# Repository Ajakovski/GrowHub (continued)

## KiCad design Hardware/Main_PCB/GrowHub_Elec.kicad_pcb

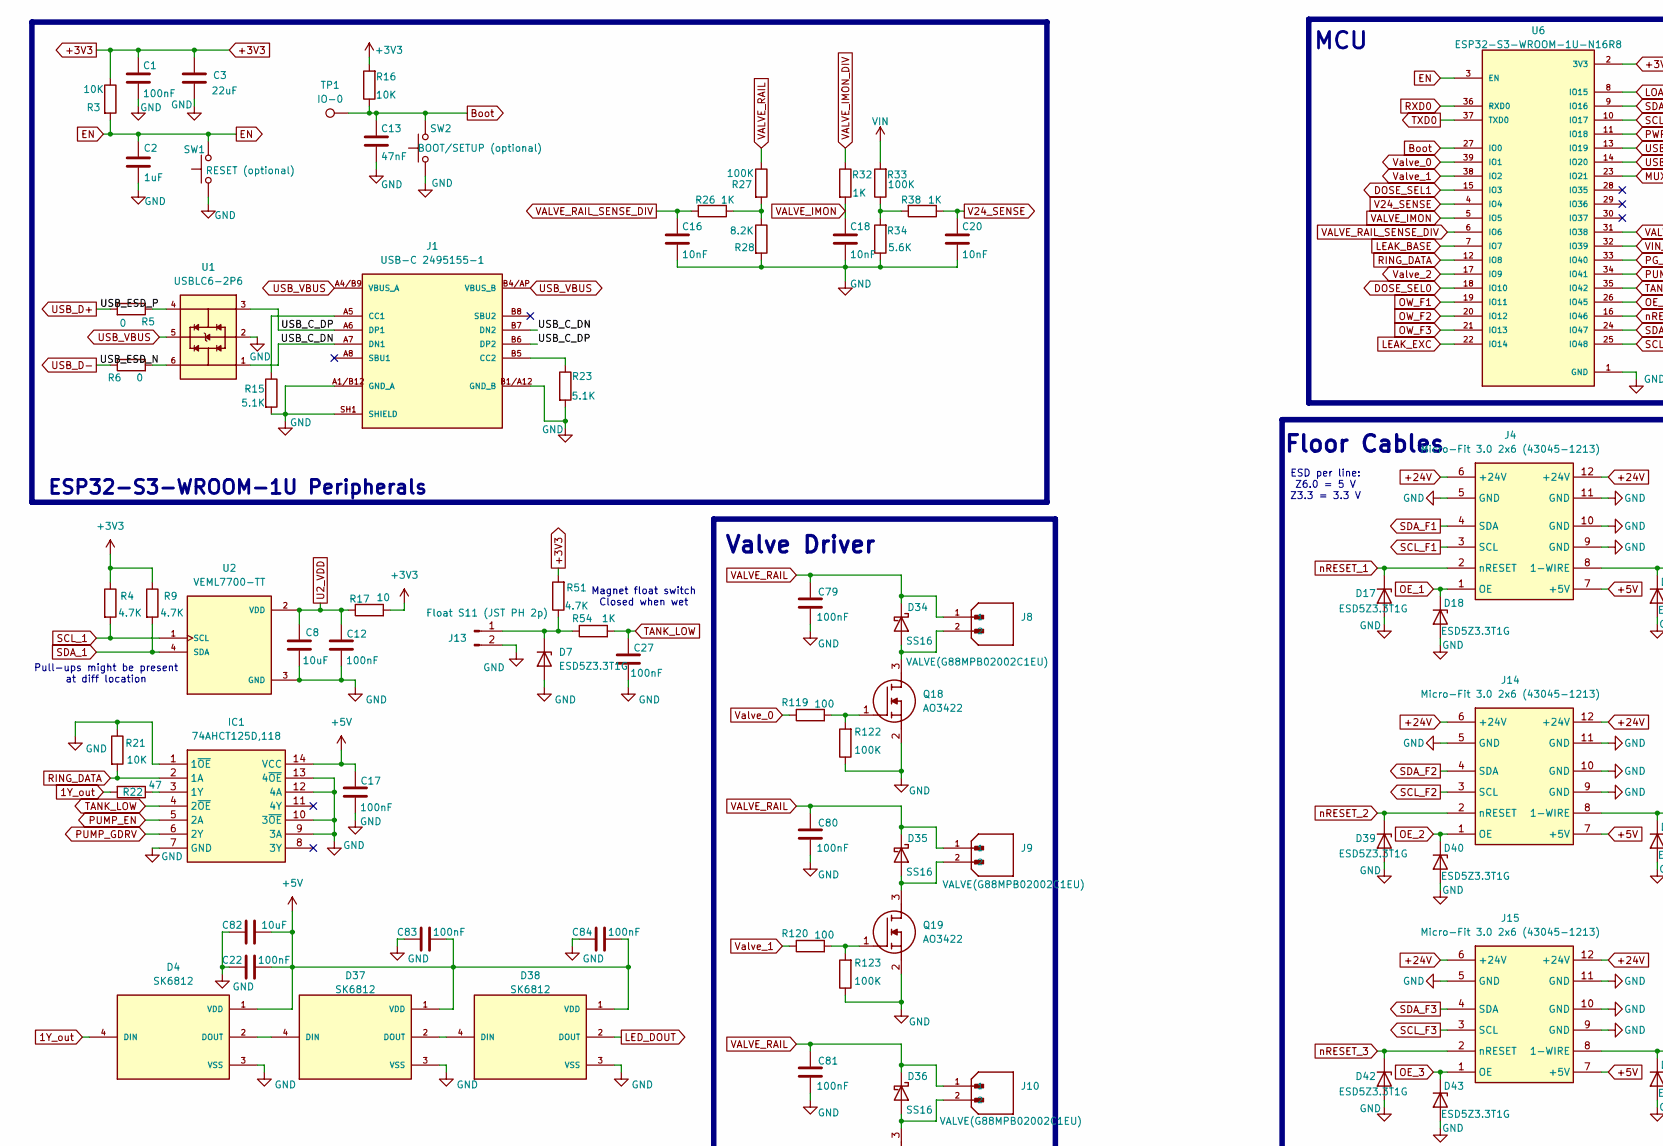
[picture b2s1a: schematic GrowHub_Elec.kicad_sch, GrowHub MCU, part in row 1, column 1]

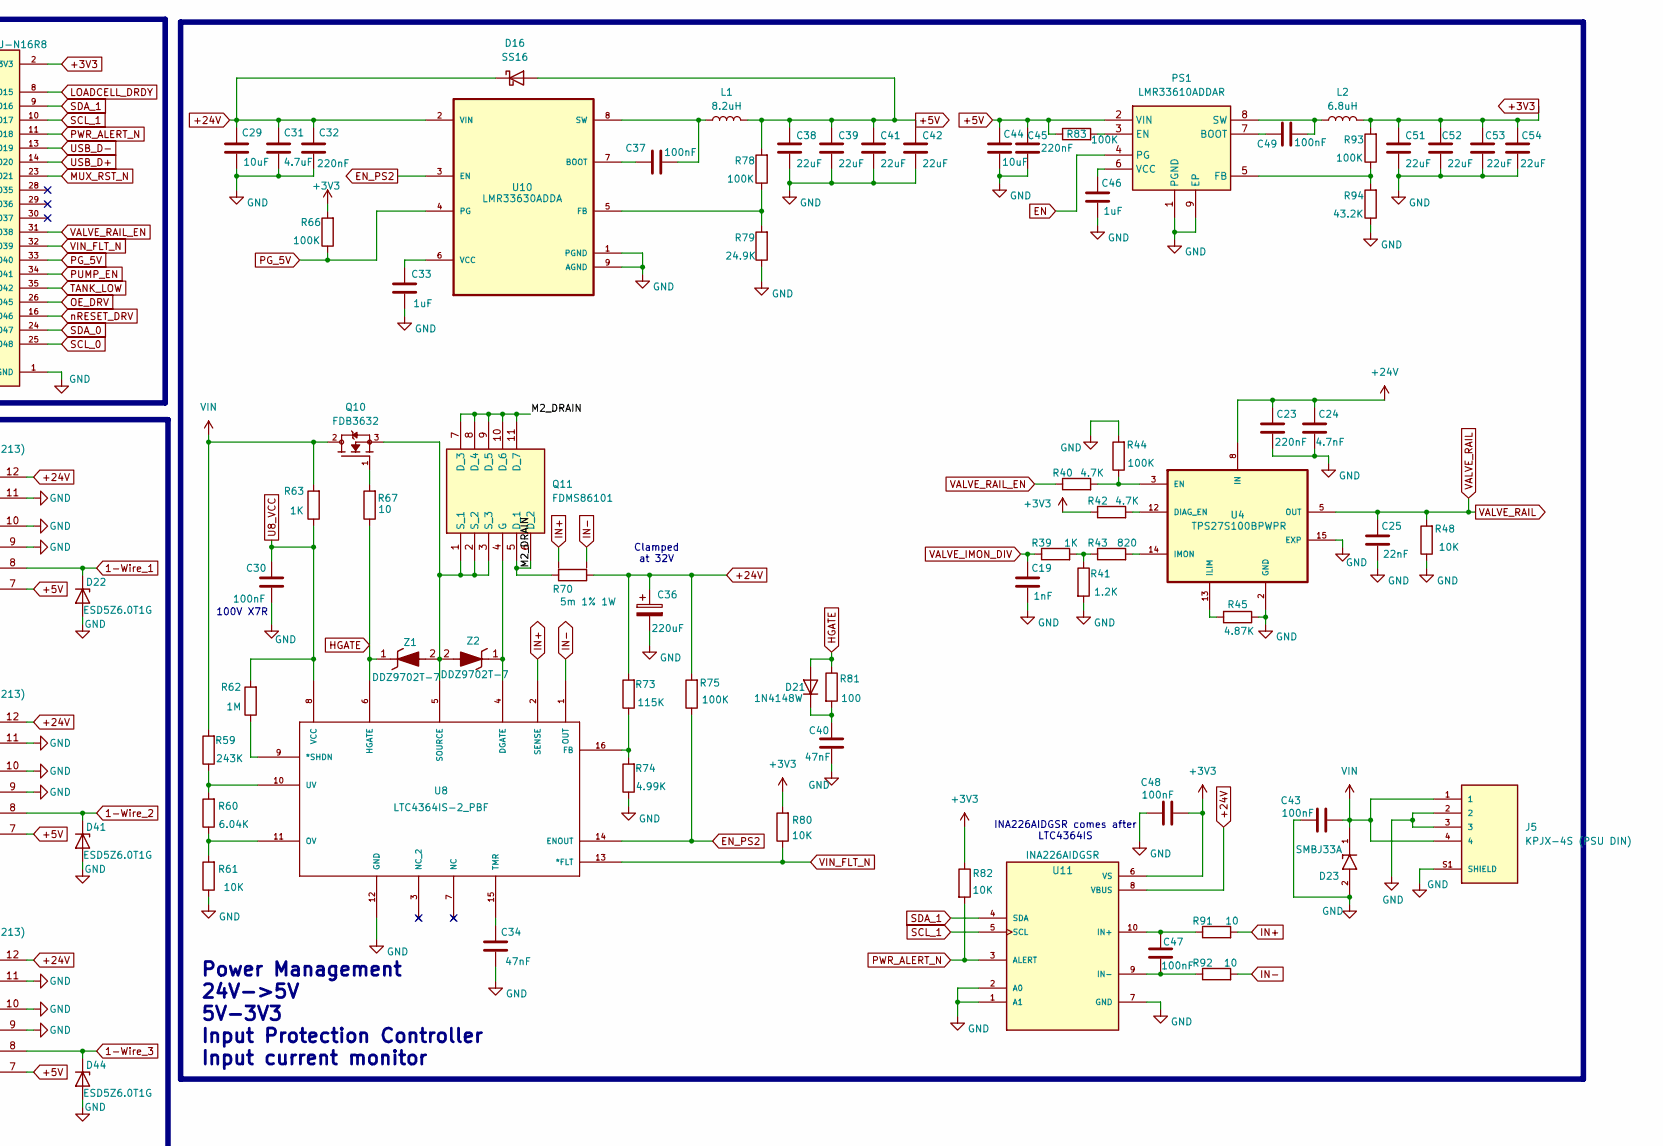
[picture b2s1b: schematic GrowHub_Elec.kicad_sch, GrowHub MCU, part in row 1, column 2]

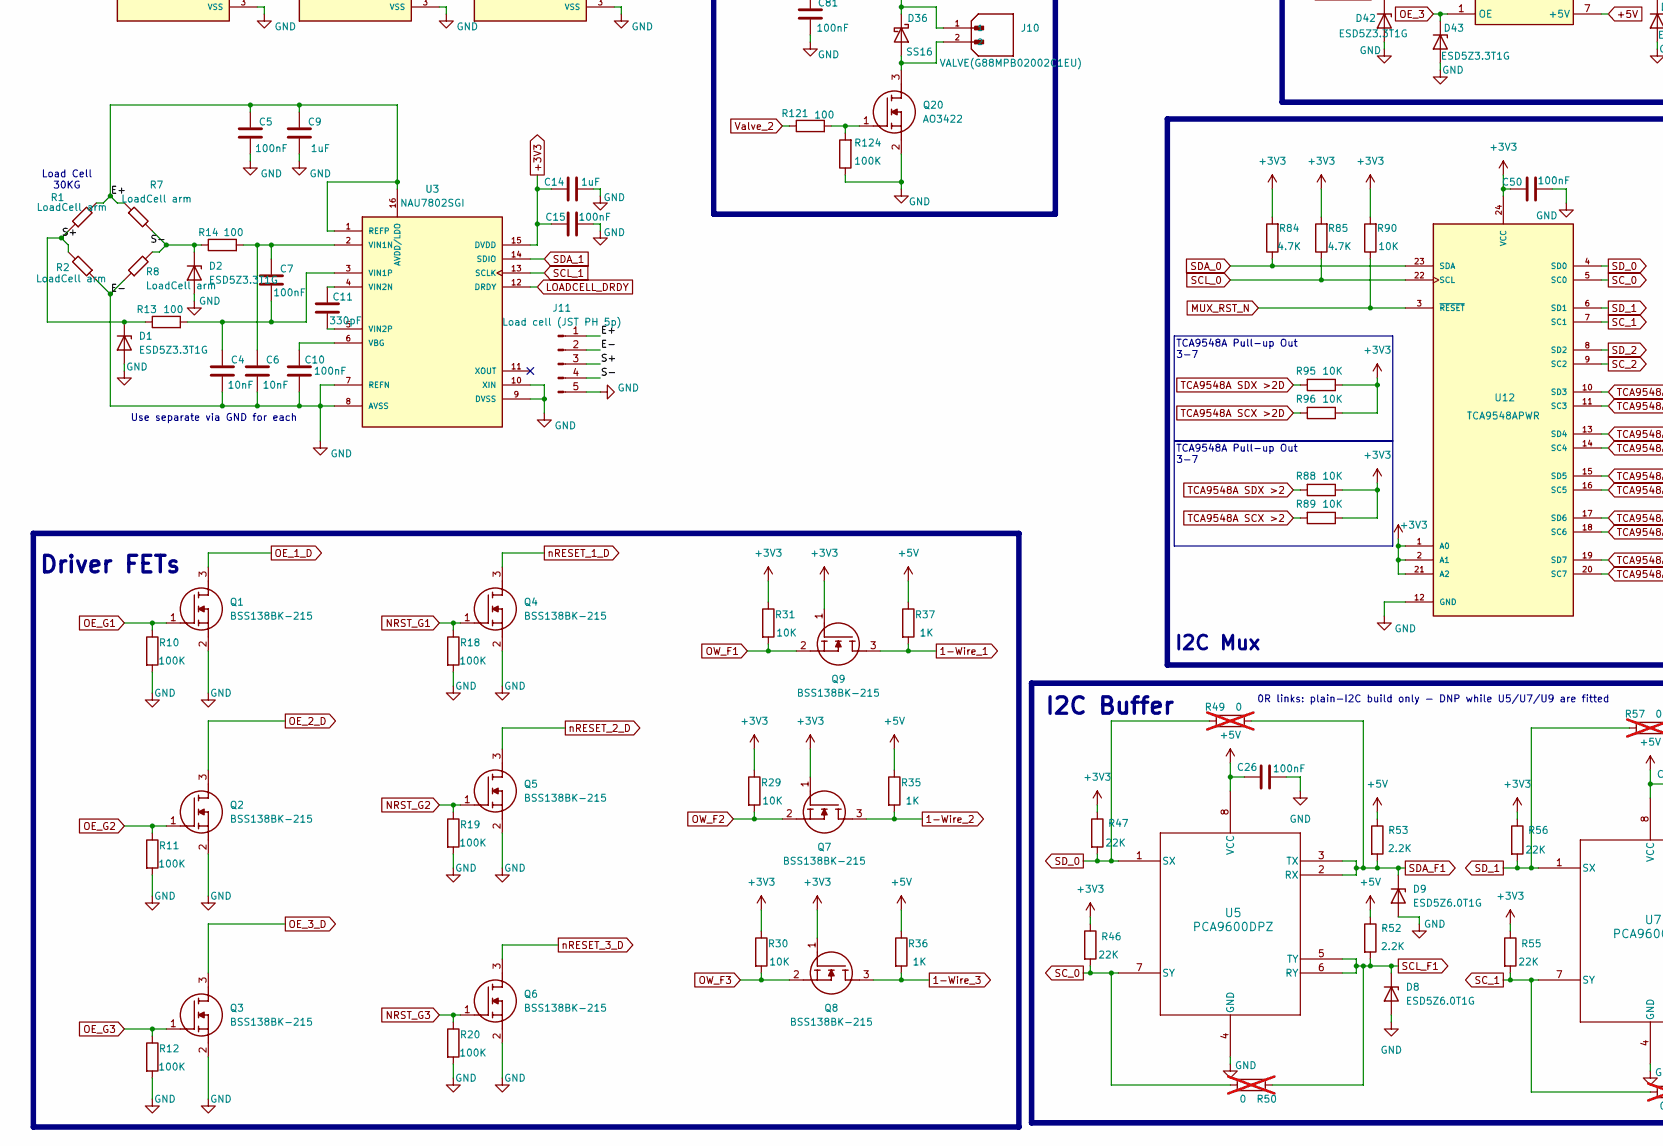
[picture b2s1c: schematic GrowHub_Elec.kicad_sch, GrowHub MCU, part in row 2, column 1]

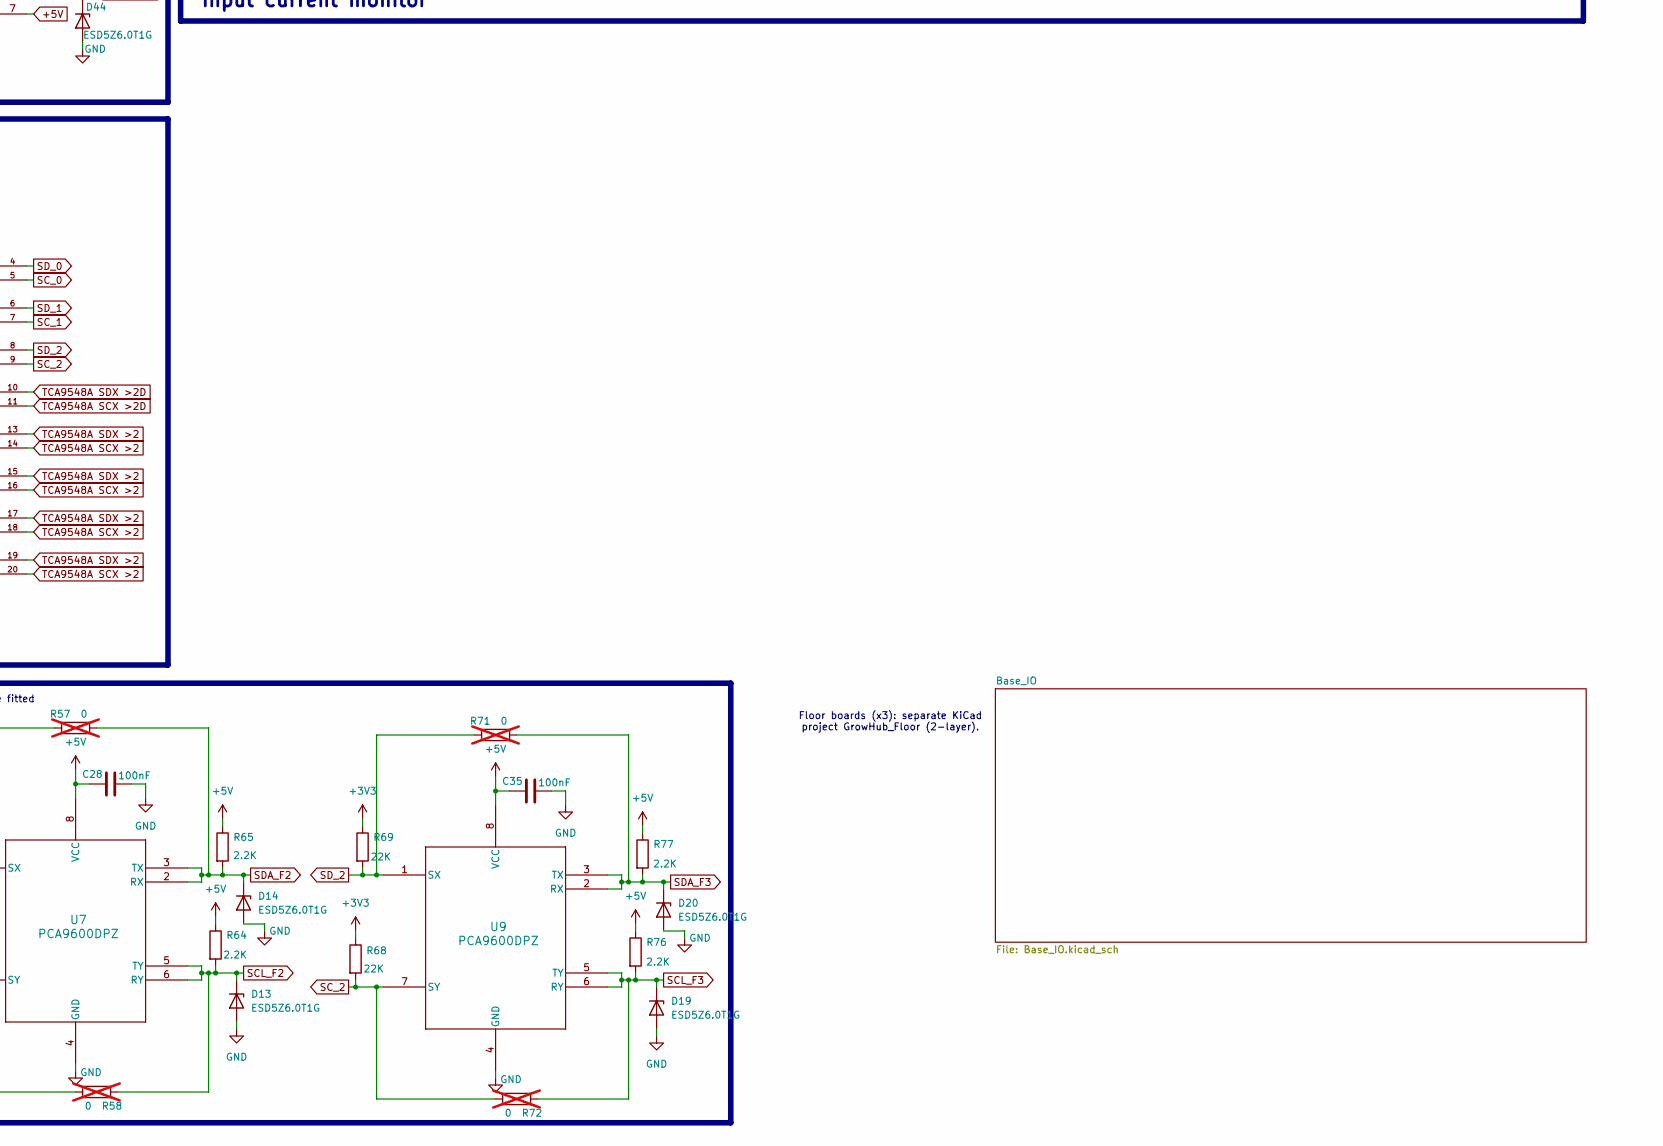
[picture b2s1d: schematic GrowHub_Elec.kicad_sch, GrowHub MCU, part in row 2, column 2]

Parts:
C1, C5, C7, C10, C12, C15, C17, C22, C26, C27, C28, C35, C37, C48, C49, C50, C83, C84: 100nF; C_0603_1608Metric; Rating 16V X7R
C2, C9, C14, C33, C46: 1uF; C_0603_1608Metric; Rating 16V X7R
C3, C51, C52, C53, C54: 22uF; C_1206_3216Metric; Rating 10V X7R
C4, C6: 10nF; C_0603_1608Metric; Rating 50V C0G
C8: 10uF; C_0805_2012Metric; Rating 10V X7R
C11: 330pF; C_0603_1608Metric; Rating 50V C0G
C13: 47nF; C_0603_1608Metric; Rating 16V X7R
C16, C18, C20: 10nF; C_0603_1608Metric; Rating 16V X7R
C19: 1nF; C_0603_1608Metric; Rating 50V C0G
C23, C32: 220nF; C_0603_1608Metric; Rating 50V X7R
C24: 4.7nF; C_0603_1608Metric; Rating 50V X7R
C25: 22nF; C_0603_1608Metric; Rating 50V X7R
C29: 10uF; C_1210_3225Metric; Rating 50V X7R
C30, C43: 100nF; C_0805_2012Metric; Rating 100V X7R
C31: 4.7uF; C_1210_3225Metric; Rating 50V X7R
C34: 47nF; C_0603_1608Metric; Rating 25V X7R
C36: 220uF; CP_Elec_10x10.5; Rating 50V low-ESR aluminium, >=105 C
C38, C39, C41, C42: 22uF; C_1206_3216Metric; Rating 16V X7R
C40: 47nF; C_0603_1608Metric; Rating 50V X7R
C44: 10uF; C_0805_2012Metric; Rating 16V X7R
C45: 220nF; C_0603_1608Metric; Rating 16V X7R
C47, C79, C80, C81: 100nF; C_0603_1608Metric; Rating 50V X7R
C82: 10uF; C_1206_3216Metric; Rating 16V X7R
D1, D2, D7, D17, D18, D39, D40, D42, D43: ESD5Z3.3T1G; D_SOD-523
D4, D37, D38: SK6812; LED_SK6812; PARTREV 03
D8, D9, D13, D14, D19, D20, D22, D41, D44: ESD5Z6.0T1G; D_SOD-523
D16, D34, D35, D36: SS16; D_SMA
D21: 1N4148W; D_SOD-123
D23: SMBJ33A; D_SMB; PARTREV 20 - 2
IC1: 74AHCT125D,118; SOIC-14_3.9x8.7mm_P1.27mm; Mouser Part Number 771-AHCT125D118
J1: USB-C 2495155-1; TE_2495155-1; PARTREV A
J4, J14, J15: Micro-Fit 3.0 2x6 (43045-1213); 0430451213; Mouser Part Number N/A
J5: KPJX-4S (PSU DIN); KYCON_KPJX-4S; PARTREV A12
J8, J9, J10: VALVE(G88MPB02002C1EU); AMPHENOL_G88MPB02002C1EU; PARTREV C
J11: Load cell (JST PH 5p); JST_PH_B5B-PH-K_1x05_P2.00mm_Vertical
J13: Float S11 (JST PH 2p); JST_PH_B2B-PH-K_1x02_P2.00mm_Vertical
L1: 8.2uH; L_Coilcraft_XAL1010-XXX; MPN Coilcraft XAL1010-822MED (12.9 mOhm max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
L2: 6.8uH; L_Coilcraft_XAL7070-XXX; MPN Coilcraft XAL7070-682MEC (19.6 mOhm max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
PS1: LMR33610ADDAR; Texas_HSOP-8-1EP_3.9x4.9mm_P1.27mm_ThermalVias; Mouser Part Number 595-LMR33610ADDAR
Q1, Q2, Q3, Q4, Q5, Q6, Q7, Q8, Q9: BSS138BK-215; SOT-23
Q10: FDB3632; TO254P1524X483-3N; PARTREV 4
Q11: FDMS86101; FDMS86252; Mouser Part Number 512-FDMS86101
Q18, Q19, Q20: AO3422; SOT-23
R1, R2, R7, R8: LoadCell arm
R3, R16, R21, R29, R30, R31, R48, R80, R82, R88, R89, R90, R95, R96: 10K; R_0603_1608Metric
R4, R9, R40, R42, R51, R84, R85: 4.7K; R_0603_1608Metric
R5, R6: 0; R_0603_1608Metric
R10, R11, R12, R18, R19, R20, R44, R66, R75, R83, R122, R123, R124: 100K; R_0603_1608Metric
R13, R14, R81, R119, R120, R121: 100; R_0603_1608Metric
R15, R23: 5.1K; R_0603_1608Metric
R17, R67, R91, R92: 10; R_0603_1608Metric
R22: 47; R_0603_1608Metric
R26, R32, R38: 1K; R_0603_1608Metric; Tolerance 1%
R27, R33, R78, R93: 100K; R_0603_1608Metric; Tolerance 1%
R28: 8.2K; R_0603_1608Metric; Tolerance 1%
R34: 5.6K; R_0603_1608Metric; Tolerance 1%
R35, R36, R37, R39, R54, R63: 1K; R_0603_1608Metric
R41: 1.2K; R_0603_1608Metric; Tolerance 1%
R43: 820; R_0603_1608Metric; Tolerance 1%
R45: 4.87K; R_0603_1608Metric; Tolerance 1%
R46, R47, R55, R56, R68, R69: 22K; R_0603_1608Metric
R49, R50, R57, R58, R71, R72: 0; R_0603_1608Metric; not fitted
R52, R53, R64, R65, R76, R77: 2.2K; R_0603_1608Metric
R59: 243K; R_0603_1608Metric; Tolerance 1%
R60: 6.04K; R_0603_1608Metric; Tolerance 1%
R61: 10K; R_0603_1608Metric; Tolerance 1%
R62: 1M; R_0603_1608Metric
R70: 5m 1% 1W; R_Shunt_Vishay_WSK2512_6332Metric_T1.19mm; MPN Vishay WSK2512R0050FEA (5 mOhm 1% 1 W, 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
R73: 115K; R_0603_1608Metric; Tolerance 1%
R74: 4.99K; R_0603_1608Metric; Tolerance 1%
R79: 24.9K; R_0603_1608Metric; Tolerance 1%
R94: 43.2K; R_0603_1608Metric; Tolerance 1%
SW1: RESET (optional); SW_SPST_TL3342
SW2: BOOT/SETUP (optional); SW_SPST_TL3342
TP1: IO-0; TestPoint_Pad_D1.5mm
U1: USBLC6-2P6; SOT-666; PARTREV 5
U2: VEML7700-TT; XDCR_VEML7700-TT; PARTREV 1.6
U3: NAU7802SGI; SOIC-16_3.9x9.9mm_P1.27mm; PARTREV 2.6
U4: TPS27S100BPWPR; IC_TPS27S100BPWPR
U5, U7, U9: PCA9600DPZ; TSSOP-8_3x3mm_P0.65mm
U6: ESP32-S3-WROOM-1U-N16R8; XCVR_ESP32-S3-WROOM-1U-N16R8; PARTREV v1.1
U8: LTC4364IS-2_PBF; SOIC-16_3.9x9.9mm_P1.27mm; MANUFACTURER_PART_NUMBER ltc4364is2#pbf
U10: LMR33630ADDA; Texas_HSOP-8-1EP_3.9x4.9mm_P1.27mm_ThermalVias
U11: INA226AIDGSR; TSSOP-10_3x3mm_P0.5mm; PARTREV B
U12: TCA9548APWR; TSSOP-24_4.4x7.8mm_P0.65mm; PARTREV G
Z1, Z2: DDZ9702T-7; D_SOD-523; Mouser Part Number 621-DDZ9702T-7

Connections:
1-Wire_1: D22.1 (K), J4.8 (1-WIRE), Q9.3 (D), R37.2
1-Wire_2: D41.1 (K), J14.8 (1-WIRE), Q7.3 (D), R35.2
1-Wire_3: D44.1 (K), J15.8 (1-WIRE), Q8.3 (D), R36.2
1Y_out: D4.4 (DIN), R22.2
+3V3: C1.1, C3.1, C14.1, C15.1, C48.1, C50.2, C51.2, C52.2, C53.2, C54.2, L2.2, Q7.1 (G), Q8.1 (G), Q9.1 (G), R3.1, R4.1, R9.1, R16.2, R17.2, R29.1, R30.1, R31.1, R42.1, R46.1, R47.1, R51.2, R55.1, R56.1, R66.2, R68.1, R69.1, R80.2, R82.1, R84.2, R85.2, R88.1, R89.1, R90.2, R93.2, R95.1, R96.1, U3.15 (DVDD), U6.2 (3V3), U11.6 (VS), U12.1 (A0), U12.2 (A1), U12.21 (A2), U12.24 (VCC); also elsewhere on the board
+5V: C17.1, C22.2, C26.2, C28.2, C35.2, C38.2, C39.2, C41.2, C42.2, C44.2, C45.2, C82.2, C83.2, C84.2, D4.1 (VDD), D16.2 (A), D37.1 (VDD), D38.1 (VDD), IC1.14 (VCC), J4.7 (+5V), J14.7 (+5V), J15.7 (+5V), L1.2, PS1.2 (VIN), R35.1, R36.1, R37.1, R52.1, R53.1, R64.1, R65.1, R76.1, R77.1, R78.2, R83.1, U5.8 (VCC), U7.8 (VCC), U9.8 (VCC); also elsewhere on the board
+24V: C23.2, C24.2, C29.2, C31.2, C32.2, C36.1, D16.1 (K), J4.6 (+24V), J4.12 (+24V), J14.6 (+24V), J14.12 (+24V), J15.6 (+24V), J15.12 (+24V), R70.4 (F2), R73.2, R75.2, U4.8 (IN), U4.9 (IN), U4.10 (IN), U10.2 (VIN), U11.8 (VBUS); also elsewhere on the board
/E+: C5.1, C9.1, J11.1 (E+), R1.2, R7.1, U3.1 (REFP), U3.16 (AVDD/LDO)
/M2_DRAIN: Q11.5 (D_1), Q11.6 (D_2), Q11.7 (D_3), Q11.8 (D_4), Q11.9 (D_5), Q11.10 (D_6), Q11.11 (D_7), R70.1 (F1)
/S+: D1.1 (K), J11.3 (S+), R1.1, R2.2, R13.1
/S-: D2.1 (K), J11.4 (S-), R7.2, R8.2, R14.1
/USB_C_DN: J1.A7 (DN1), J1.B7 (DN2), U1.1
/USB_C_DP: J1.A6 (DP1), J1.B6 (DP2), U1.3
/USB_ESD_N: R6.2, U1.6
/USB_ESD_P: R5.1, U1.4
Boot: C13.1, R16.1, SW2.2, TP1.1 (1_1), U6.27 (IO0)
DOSE_SEL0: U6.18 (IO10)
DOSE_SEL1: U6.15 (IO3)
EN: C2.1, PS1.4 (PG), R3.2, SW1.2, U6.3 (EN); also elsewhere on the board
EN_PS2: R75.1, U8.14 (ENOUT), U10.3 (EN)
GND: C1.2, C2.2, C3.2, C4.2, C5.2, C6.2, C8.2, C9.2, C10.2, C12.2, C13.2, C14.2, C15.2, C16.2, C17.2, C18.2, C19.1, C20.2, C22.1, C23.1, C24.1, C25.1, C26.1, C27.2, C28.1, C29.1, C30.2, C31.1, C32.1, C33.2, C34.2, C35.1, C36.2, C38.1, C39.1, C40.2, C41.1, C42.1, C43.2, C44.1, C45.1, C46.1, C48.2, C50.1, C51.1, C52.1, C53.1, C54.1, C79.2, C80.2, C81.2, C82.1, C83.1, C84.1, D1.2 (A), D2.2 (A), D4.3 (VSS), D7.2 (A), D8.2 (A), D9.2 (A), D13.2 (A), D14.2 (A), D17.2 (A), D18.2 (A), D19.2 (A), D20.2 (A), D22.2 (A), D23.2, D37.3 (VSS), D38.3 (VSS), D39.2 (A), D40.2 (A), D41.2 (A), D42.2 (A), D43.2 (A), D44.2 (A), IC1.1 (1~OE), IC1.7 (GND), IC1.9 (3A), IC1.10 (3~OE), IC1.12 (4A), IC1.13 (4~OE), J1.A1/B12 (GND_A), J1.B1/A12 (GND_B), J1.SH1 (SHIELD), J1.SH2 (SHIELD), J1.SH3 (SHIELD), J1.SH4 (SHIELD), J4.5 (GND), J4.9 (GND), J4.10 (GND), J4.11 (GND), J5.2, J5.3, J5.S1 (SHIELD), J11.2 (E-), J11.5 (SH), J13.2, J14.5 (GND), J14.9 (GND), J14.10 (GND), J14.11 (GND), J15.5 (GND), J15.9 (GND), J15.10 (GND), J15.11 (GND), PS1.1 (PGND), PS1.9 (EP), Q1.2 (S), Q2.2 (S), Q3.2 (S), Q4.2 (S), Q5.2 (S), Q6.2 (S), Q18.2 (S), Q19.2 (S), Q20.2 (S), R2.1, R8.1, R10.2, R11.2, R12.2, R15.2, R18.2, R19.2, R20.2, R21.1, R23.2, R28.2, R34.1, R41.2, R44.2, R45.1, R48.1, R61.1, R74.1, R79.1, R94.1, R122.1, R123.1, R124.1, SW1.1, SW2.1, U1.2, U2.3 (GND), U3.7 (REFN), U3.8 (AVSS), U3.9 (DVSS), U3.10 (XIN), U4.2 (GND), U4.15 (EXP), U4.16 (EXP), U4.17 (EXP), U4.18 (EXP), U4.19 (EXP), U4.20 (EXP), U4.21 (EXP), U5.4 (GND), U6.1 (GND), U6.40 (GND), U6.41_1 (GND), U6.41_2 (GND), U6.41_3 (GND), U6.41_4 (GND), U6.41_5 (GND), U6.41_6 (GND), U6.41_7 (GND), U6.41_8 (GND), U6.41_9 (GND), U7.4 (GND), U8.12 (GND), U9.4 (GND), U10.1 (PGND), U10.9 (AGND), U11.1 (A1), U11.2 (A0), U11.7 (GND), U12.12 (GND); also elsewhere on the board
HGATE: D21.2 (A), R67.1, R81.1, U8.6 (HGATE), Z1.1 (K)
IN+: R70.2 (S1), R91.2, U8.2 (SENSE)
IN-: R70.3 (S2), R92.2, U8.1 (OUT)
LEAK_BASE: U6.7 (IO7); also elsewhere on the board
LEAK_EXC: U6.22 (IO14); also elsewhere on the board
LED_DOUT: D38.2 (DOUT); also elsewhere on the board
LOADCELL_DRDY: U3.12 (DRDY), U6.8 (IO15)
MUX_RST_N: R90.1, U6.23 (IO21), U12.3 (~RESET)
NRST_G1: Q4.1 (G), R18.1; also elsewhere on the board
NRST_G2: Q5.1 (G), R19.1; also elsewhere on the board
NRST_G3: Q6.1 (G), R20.1; also elsewhere on the board
unnamed: D7.1 (K), J13.1, R51.1, R54.1
unnamed: C40.1, D21.1 (K), R81.2
unnamed: D34.2 (A), J8.2, Q18.3 (D)
unnamed: D35.2 (A), J9.2, Q19.3 (D)
unnamed: D36.2 (A), J10.2, Q20.3 (D)
unnamed: D4.2 (DOUT), D37.4 (DIN)
unnamed: D37.2 (DOUT), D38.4 (DIN)
unnamed: IC1.3 (1Y), R22.1
unnamed: J1.A5 (CC1), R15.1
unnamed: J1.B5 (CC2), R23.1
unnamed: C49.2, PS1.7 (BOOT)
unnamed: PS1.3 (EN), R83.2
unnamed: PS1.5 (FB), R93.1, R94.2
unnamed: C49.1, L2.1, PS1.8 (SW)
unnamed: C46.2, PS1.6 (VCC)
unnamed: Q10.1, R67.2
unnamed: Q11.4 (G), U8.4 (DGATE), Z2.1 (K)
unnamed: Q10.3, Q11.1 (S_1), Q11.2 (S_2), Q11.3 (S_3), U8.5 (SOURCE), Z1.2 (A), Z2.2 (A)
unnamed: Q18.1 (G), R119.2, R122.2
unnamed: Q19.1 (G), R120.2, R123.2
unnamed: Q20.1 (G), R121.2, R124.2
unnamed: R26.1, R27.2, R28.1
unnamed: R33.1, R34.2, R38.2
unnamed: R39.2, R41.1, R43.1
unnamed: C10.1, U3.6 (VBG)
unnamed: C6.1, C7.1, R14.2, U3.2 (VIN1N)
unnamed: C4.1, C7.2, R13.2, U3.3 (VIN1P)
unnamed: C11.1, U3.4 (VIN2N)
unnamed: C11.2, U3.5 (VIN2P)
unnamed: R42.2, U4.12 (DIAG_EN)
unnamed: R40.2, R44.1, U4.3 (EN)
unnamed: R45.2, U4.13 (ILIM)
unnamed: R43.2, U4.14 (IMON)
unnamed: R62.1, U8.9 (*SHDN)
unnamed: R73.1, R74.2, U8.16 (FB)
unnamed: R60.1, R61.2, U8.11 (OV)
unnamed: C34.1, U8.15 (TMR)
unnamed: R59.1, R60.2, U8.10 (UV)
unnamed: C37.2, U10.7 (BOOT)
unnamed: R78.1, R79.2, U10.5 (FB)
unnamed: C37.1, L1.1, U10.8 (SW)
unnamed: C33.1, U10.6 (VCC)
unnamed: C47.1, R91.1, U11.10 (IN+)
unnamed: C47.2, R92.1, U11.9 (IN-)
OE_1: D18.1 (K), J4.1 (OE); also elsewhere on the board
OE_1_D: Q1.3 (D); also elsewhere on the board
OE_2: D40.1 (K), J14.1 (OE); also elsewhere on the board
OE_2_D: Q2.3 (D); also elsewhere on the board
OE_3: D43.1 (K), J15.1 (OE); also elsewhere on the board
OE_3_D: Q3.3 (D); also elsewhere on the board
OE_DRV: U6.26 (IO45); also elsewhere on the board
OE_G1: Q1.1 (G), R10.1; also elsewhere on the board
OE_G2: Q2.1 (G), R11.1; also elsewhere on the board
OE_G3: Q3.1 (G), R12.1; also elsewhere on the board
OW_F1: Q9.2 (S), R31.2, U6.19 (IO11)
OW_F2: Q7.2 (S), R29.2, U6.20 (IO12)
OW_F3: Q8.2 (S), R30.2, U6.21 (IO13)
PG_5V: R66.1, U6.33 (IO40), U10.4 (PG)
PUMP_EN: IC1.5 (2A), U6.34 (IO41); also elsewhere on the board
PUMP_GDRV: IC1.6 (2Y); also elsewhere on the board
PWR_ALERT_N: R82.2, U6.11 (IO18), U11.3 (ALERT)
RING_DATA: IC1.2 (1A), R21.2, U6.12 (IO8)
RXD0: U6.36 (RXD0); also elsewhere on the board
SCL_0: R85.1, U6.25 (IO48), U12.22 (SCL)
SCL_1: R4.2, U2.1 (SCL), U3.13 (SCLK), U6.10 (IO17), U11.5 (SCL)
SCL_F1: D8.1 (K), J4.3 (SCL), R50.2, R52.2, U5.5 (TY), U5.6 (RY)
SCL_F2: D13.1 (K), J14.3 (SCL), R58.2, R64.2, U7.5 (TY), U7.6 (RY)
SCL_F3: D19.1 (K), J15.3 (SCL), R72.2, R76.2, U9.5 (TY), U9.6 (RY)
SC_0: R46.2, R50.1, U5.7 (SY), U12.5 (SC0)
SC_1: R55.2, R58.1, U7.7 (SY), U12.7 (SC1)
SC_2: R68.2, R72.1, U9.7 (SY), U12.9 (SC2)
SDA_0: R84.1, U6.24 (IO47), U12.23 (SDA)
SDA_1: R9.2, U2.4 (SDA), U3.14 (SDIO), U6.9 (IO16), U11.4 (SDA)
SDA_F1: D9.1 (K), J4.4 (SDA), R49.1, R53.2, U5.2 (RX), U5.3 (TX)
SDA_F2: D14.1 (K), J14.4 (SDA), R57.1, R65.2, U7.2 (RX), U7.3 (TX)
SDA_F3: D20.1 (K), J15.4 (SDA), R71.1, R77.2, U9.2 (RX), U9.3 (TX)
SD_0: R47.2, R49.2, U5.1 (SX), U12.4 (SD0)
SD_1: R56.2, R57.2, U7.1 (SX), U12.6 (SD1)
SD_2: R69.2, R71.2, U9.1 (SX), U12.8 (SD2)
TANK_LOW: C27.1, IC1.4 (2~OE), R54.2, U6.35 (IO42)
TCA9548A SCX >2: R89.2, U12.14 (SC4), U12.16 (SC5), U12.18 (SC6), U12.20 (SC7)
TCA9548A SCX >2D: R96.2, U12.11 (SC3)
TCA9548A SDX >2: R88.2, U12.13 (SD4), U12.15 (SD5), U12.17 (SD6), U12.19 (SD7)
TCA9548A SDX >2D: R95.2, U12.10 (SD3)
TXD0: U6.37 (TXD0); also elsewhere on the board
U2_VDD: C8.1, C12.1, R17.1, U2.2 (VDD)
U8_VCC: C30.1, R62.2, R63.1, U8.8 (VCC)
USB_D+: R5.2, U6.14 (IO20)
USB_D-: R6.1, U6.13 (IO19)
USB_VBUS: J1.A4/B9 (VBUS_A), J1.B4/AP (VBUS_B), U1.5
V24_SENSE: C20.1, R38.1, U6.4 (IO4)
VALVE_IMON: C18.1, R32.2, U6.5 (IO5)
VALVE_IMON_DIV: C19.2, R32.1, R39.1
VALVE_RAIL: C25.2, C79.1, C80.1, C81.1, D34.1 (K), D35.1 (K), D36.1 (K), J8.1, J9.1, J10.1, R27.1, R48.2, U4.5 (OUT), U4.6 (OUT), U4.7 (OUT)
VALVE_RAIL_EN: R40.1, U6.31 (IO38)
VALVE_RAIL_SENSE_DIV: C16.1, R26.2, U6.6 (IO6)
VIN: C43.1, D23.1, J5.1, J5.4, Q10.2, R33.2, R59.2, R63.2; also elsewhere on the board
VIN_FLT_N: R80.1, U6.32 (IO39), U8.13 (*FLT)
Valve_0: R119.1, U6.39 (IO1)
Valve_1: R120.1, U6.38 (IO2)
Valve_2: R121.1, U6.17 (IO9)
nRESET_1: D17.1 (K), J4.2 (nRESET); also elsewhere on the board
nRESET_1_D: Q4.3 (D); also elsewhere on the board
nRESET_2: D39.1 (K), J14.2 (nRESET); also elsewhere on the board
nRESET_2_D: Q5.3 (D); also elsewhere on the board
nRESET_3: D42.1 (K), J15.2 (nRESET); also elsewhere on the board
nRESET_3_D: Q6.3 (D); also elsewhere on the board
nRESET_DRV: U6.16 (IO46); also elsewhere on the board

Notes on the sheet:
Valve Driver
Pull-ups might be present at diff location
0R links: plain-I2C build only - DNP while U5/U7/U9 are fitted
Load Cell 30KG
100V X7R
Use separate via GND for each
INA226AIDGSR comes after LTC4364IS
TCA9548A Pull-up Out 3-7
Clamped at 32V
Floor Cables
Driver FETs
ESP32-S3-WROOM-1U Peripherals
ESD per line: Z6.0 = 5 V Z3.3 = 3.3 V
MCU
Magnet float switch Closed when wet
I2C Mux
I2C Buffer
Power Management 24V->5V 5V-3V3 Input Protection Controller Input current monitor
Floor boards (x3): separate KiCad project GrowHub_Floor (2-layer).

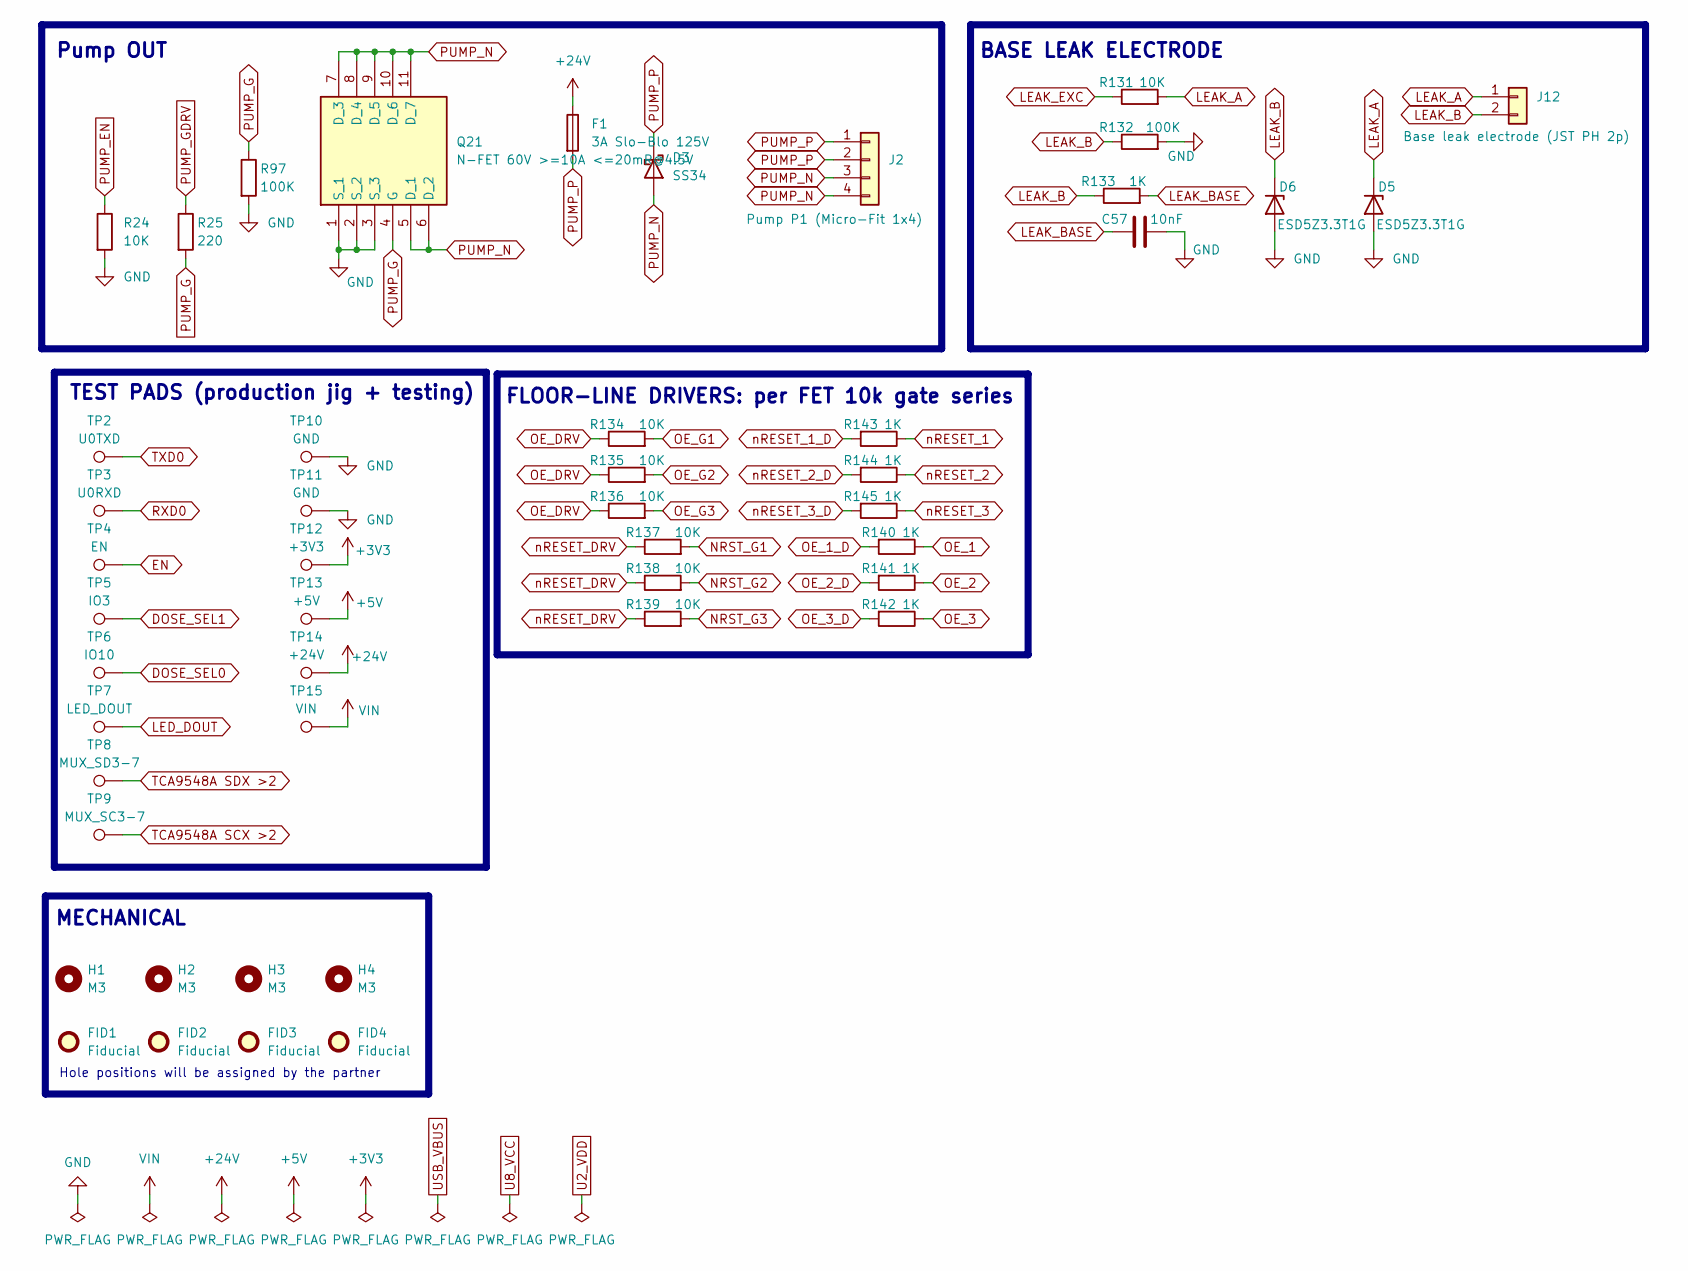
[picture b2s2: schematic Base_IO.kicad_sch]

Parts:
C57: 10nF; C_0603_1608Metric; Rating 16V X7R
D3: SS34; D_SMA
D5, D6: ESD5Z3.3T1G; D_SOD-523
F1: 3A Slo-Blo 125V; Fuse_Littelfuse-NANO2-451_453; Rating 3 A time-lag, 125 V, 50 A interrupting;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; MPN Littelfuse 0454003.MR (NANO2 454, 2410)
FID1, FID2, FID3, FID4: Fiducial; Fiducial_1mm_Mask2mm
H1, H2, H3, H4: M3; MountingHole_3.2mm_M3
J2: Pump P1 (Micro-Fit 1x4); Molex_Micro-Fit_3.0_43650-0400_1x04_P3.00mm_Horizontal
J12: Base leak electrode (JST PH 2p); JST_PH_B2B-PH-K_1x02_P2.00mm_Vertical
Q21: N-FET 60V >=10A <=20mR@4.5V; FDMS86252; Mouser Part Number 512-FDMS86500L
R24, R131, R134, R135, R136, R137, R138, R139: 10K; R_0603_1608Metric
R25: 220; R_0603_1608Metric
R97, R132: 100K; R_0603_1608Metric
R133: 1K; R_0603_1608Metric
R140, R141, R142, R143, R144, R145: 1K; R_2010_5025Metric
TP2: U0TXD; TestPoint_Pad_D1.5mm
TP3: U0RXD; TestPoint_Pad_D1.5mm
TP4: EN; TestPoint_Pad_D1.5mm
TP5: IO3; TestPoint_Pad_D1.5mm
TP6: IO10; TestPoint_Pad_D1.5mm
TP7: LED_DOUT; TestPoint_Pad_D1.5mm
TP8: MUX_SD3-7; TestPoint_Pad_D1.5mm
TP9: MUX_SC3-7; TestPoint_Pad_D1.5mm
TP10, TP11: GND; TestPoint_Pad_D1.5mm
TP12: +3V3; TestPoint_Pad_D1.5mm
TP13: +5V; TestPoint_Pad_D1.5mm
TP14: +24V; TestPoint_Pad_D1.5mm
TP15: VIN; TestPoint_Pad_D1.5mm

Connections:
+3V3: TP12.1 (1_1); also elsewhere on the board
+5V: TP13.1 (1_1); also elsewhere on the board
+24V: F1.1, TP14.1 (1_1); also elsewhere on the board
EN: TP4.1 (1_1); also elsewhere on the board
GND: C57.2, D5.2 (A), D6.2 (A), Q21.1 (S_1), Q21.2 (S_2), Q21.3 (S_3), R24.2, R97.2, R132.2, TP10.1 (1_1), TP11.1 (1_1); also elsewhere on the board
LEAK_A: D5.1 (K), J12.1, R131.2
LEAK_B: D6.1 (K), J12.2, R132.1, R133.1
LEAK_BASE: C57.1, R133.2; also elsewhere on the board
LEAK_EXC: R131.1; also elsewhere on the board
LED_DOUT: TP7.1 (1_1); also elsewhere on the board
NRST_G1: R137.2; also elsewhere on the board
NRST_G2: R138.2; also elsewhere on the board
NRST_G3: R139.2; also elsewhere on the board
OE_1: R140.1; also elsewhere on the board
OE_1_D: R140.2; also elsewhere on the board
OE_2: R141.1; also elsewhere on the board
OE_2_D: R141.2; also elsewhere on the board
OE_3: R142.1; also elsewhere on the board
OE_3_D: R142.2; also elsewhere on the board
OE_DRV: R134.1, R135.1, R136.1; also elsewhere on the board
OE_G1: R134.2; also elsewhere on the board
OE_G2: R135.2; also elsewhere on the board
OE_G3: R136.2; also elsewhere on the board
PUMP_EN: R24.1; also elsewhere on the board
PUMP_G: Q21.4 (G), R25.2, R97.1
PUMP_GDRV: R25.1; also elsewhere on the board
PUMP_N: D3.2 (A), J2.3, J2.4, Q21.5 (D_1), Q21.6 (D_2), Q21.7 (D_3), Q21.8 (D_4), Q21.9 (D_5), Q21.10 (D_6), Q21.11 (D_7)
PUMP_P: D3.1 (K), F1.2, J2.1, J2.2
RXD0: TP3.1 (1_1); also elsewhere on the board
TXD0: TP2.1 (1_1); also elsewhere on the board
VIN: TP15.1 (1_1); also elsewhere on the board
nRESET_1: R143.1; also elsewhere on the board
nRESET_1_D: R143.2; also elsewhere on the board
nRESET_2: R144.1; also elsewhere on the board
nRESET_2_D: R144.2; also elsewhere on the board
nRESET_3: R145.1; also elsewhere on the board
nRESET_3_D: R145.2; also elsewhere on the board
nRESET_DRV: R137.1, R138.1, R139.1; also elsewhere on the board

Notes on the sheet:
FLOOR-LINE DRIVERS: per FET 10k gate series
TEST PADS (production jig + testing)
BASE LEAK ELECTRODE
Pump OUT
MECHANICAL
Hole positions will be assigned by the partner

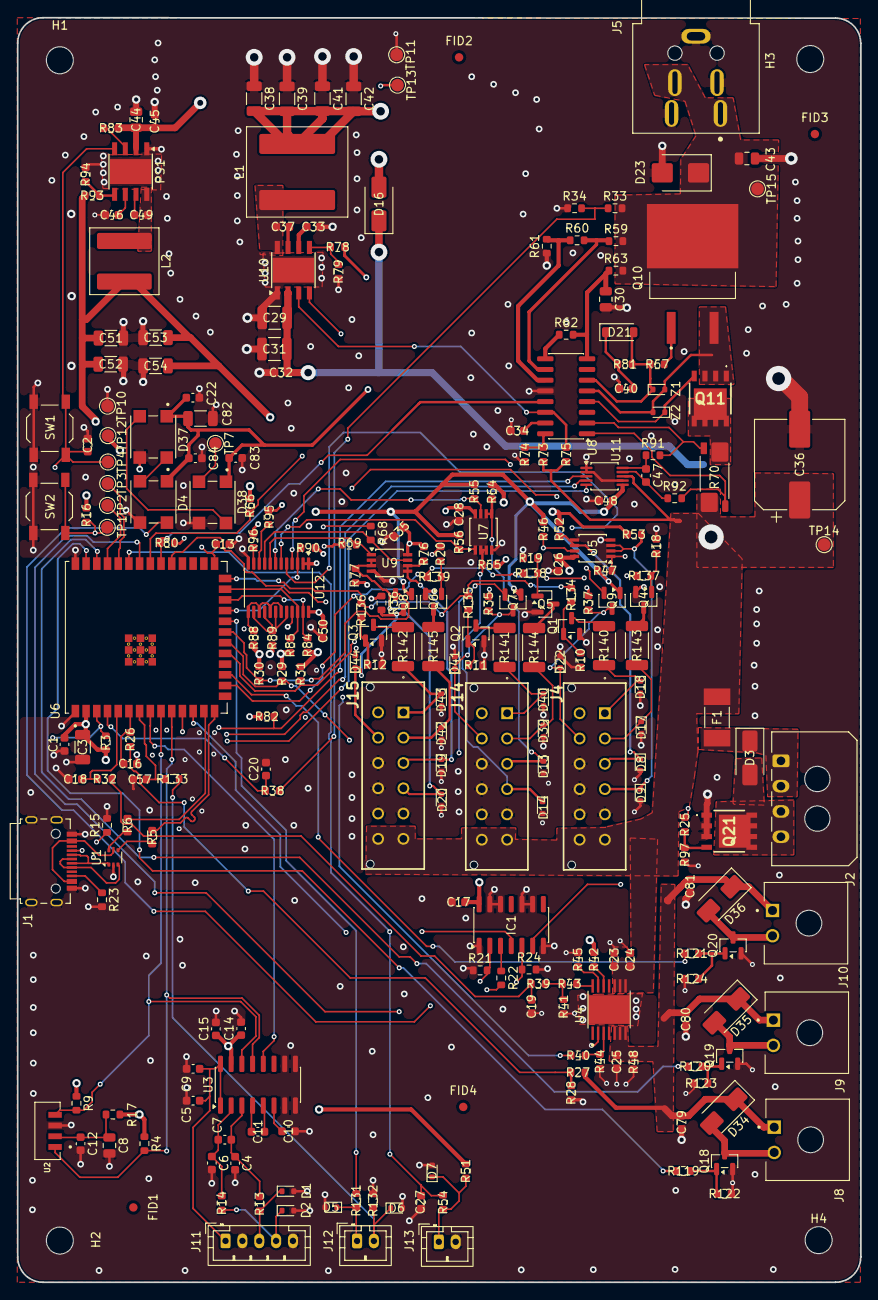
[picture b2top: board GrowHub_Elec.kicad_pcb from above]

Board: 4 copper layers, 100.0 x 150.0 mm, 263 parts (0 on the bottom side), 143 nets.
